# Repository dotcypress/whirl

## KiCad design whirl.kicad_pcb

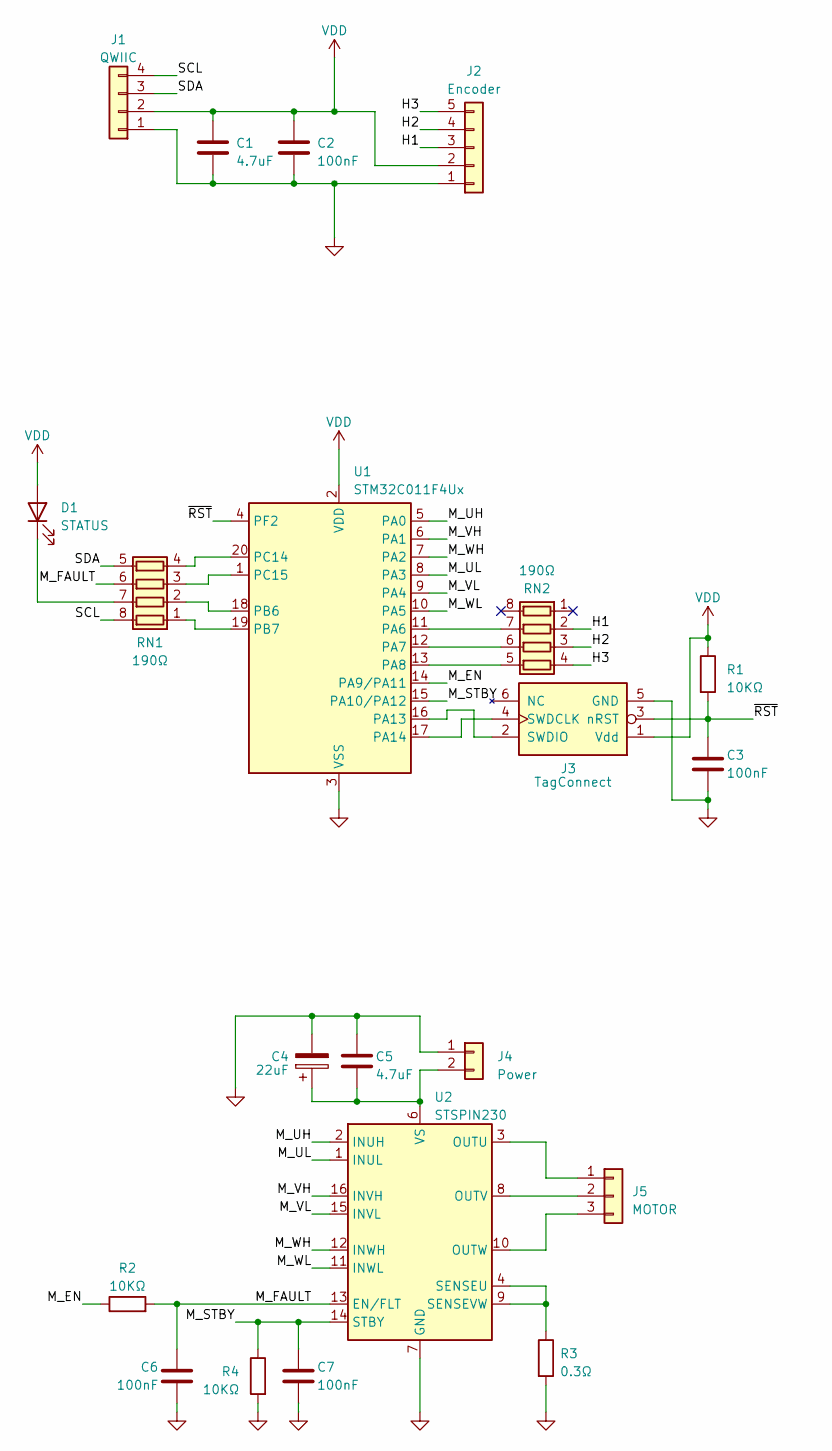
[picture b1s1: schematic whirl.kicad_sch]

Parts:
C1, C5: 4.7uF; C_0603_1608Metric
C2, C3, C6, C7: 100nF; C_0603_1608Metric
C4: 22uF; C_1210_3225Metric
D1: STATUS; LED_0603_1608Metric
J1: QWIIC; JST_SH_SM04B-SRSS-TB_1x04-1MP_P1.00mm_Horizontal
J2: Encoder; JST_SH_SM05B-SRSS-TB_1x05-1MP_P1.00mm_Horizontal
J3: TagConnect; Tag-Connect_TC2030-IDC-NL_2x03_P1.27mm_Vertical
J4: Power; PinHeader_1x02_P2.54mm_Vertical
J5: MOTOR; PinHeader_1x03_P2.54mm_Vertical
R1, R2, R4: 10KΩ; R_0603_1608Metric
R3: 0.3Ω; R_1206_3216Metric
RN1, RN2: 190Ω; R_Array_Convex_4x0603
U1: STM32C011F4Ux; ST_UFQFPN-20_3x3mm_P0.5mm
U2: STSPIN230; VQFN-16-1EP_3x3mm_P0.5mm_EP1.8x1.8mm

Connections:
/H1: J2.3, RN2.2 (R2.1)
/H2: J2.4, RN2.3 (R3.1)
/H3: J2.5, RN2.4 (R4.1)
/M_EN: R2.1, U1.14 (PA9/PA11)
/M_FAULT: C6.1, R2.2, RN1.6 (R3.2), U2.13 (EN/FLT)
/M_STBY: C7.1, R4.1, U1.15 (PA10/PA12), U2.14 (STBY)
/M_UH: U1.5 (PA0), U2.2 (INUH)
/M_UL: U1.8 (PA3), U2.1 (INUL)
/M_VH: U1.6 (PA1), U2.16 (INVH)
/M_VL: U1.9 (PA4), U2.15 (INVL)
/M_WH: U1.7 (PA2), U2.12 (INWH)
/M_WL: U1.10 (PA5), U2.11 (INWL)
/SCL: J1.4, RN1.8 (R1.2)
/SDA: J1.3, RN1.5 (R4.2)
/~RST: C3.1, J3.3 (nRST), R1.2, U1.4 (PF2)
GND: C1.2, C2.2, C3.2, C4.2, C5.2, C6.2, C7.2, J1.1, J2.1, J3.5 (GND), J4.1, R3.2, R4.2, U1.3 (VSS), U2.7 (GND), U2.17 (GND)
unnamed: D1.1 (K), RN1.7 (R2.2)
unnamed: J3.4 (SWDCLK), U1.17 (PA14)
unnamed: J3.2 (SWDIO), U1.16 (PA13)
unnamed: C4.1, C5.1, J4.2, U2.6 (VS)
unnamed: J5.1, U2.3 (OUTU)
unnamed: J5.2, U2.8 (OUTV)
unnamed: J5.3, U2.10 (OUTW)
unnamed: RN1.1 (R1.1), U1.19 (PB7)
unnamed: RN1.2 (R2.1), U1.18 (PB6)
unnamed: RN1.3 (R3.1), U1.1 (PC15)
unnamed: RN1.4 (R4.1), U1.20 (PC14)
unnamed: RN2.7 (R2.2), U1.11 (PA6)
unnamed: RN2.6 (R3.2), U1.12 (PA7)
unnamed: RN2.5 (R4.2), U1.13 (PA8)
unnamed: R3.1, U2.4 (SENSEU), U2.9 (SENSEVW)
VDD: C1.1, C2.1, D1.2 (A), J1.2, J2.2, J3.1 (Vdd), R1.1, U1.2 (VDD)

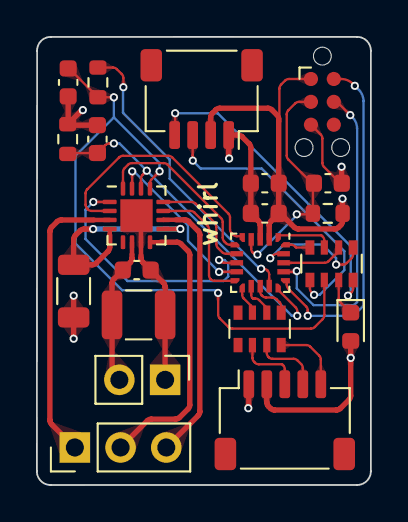
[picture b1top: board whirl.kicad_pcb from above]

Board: 4 copper layers, 18.6 x 24.9 mm, 21 parts (0 on the bottom side), 32 nets.

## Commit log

2023-03-12 rev:0x01
2023-03-26 rev:0x02
